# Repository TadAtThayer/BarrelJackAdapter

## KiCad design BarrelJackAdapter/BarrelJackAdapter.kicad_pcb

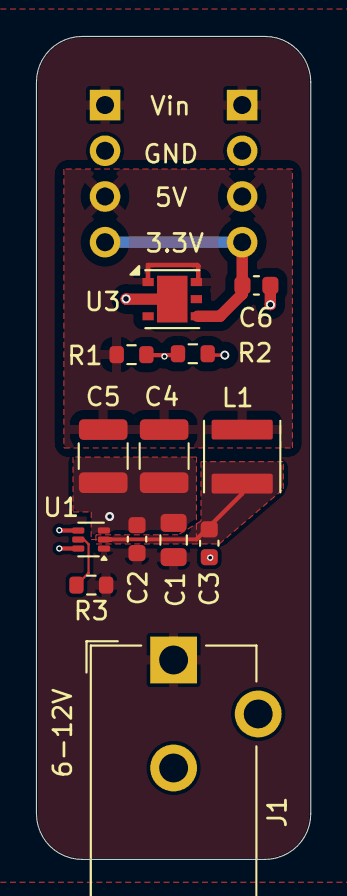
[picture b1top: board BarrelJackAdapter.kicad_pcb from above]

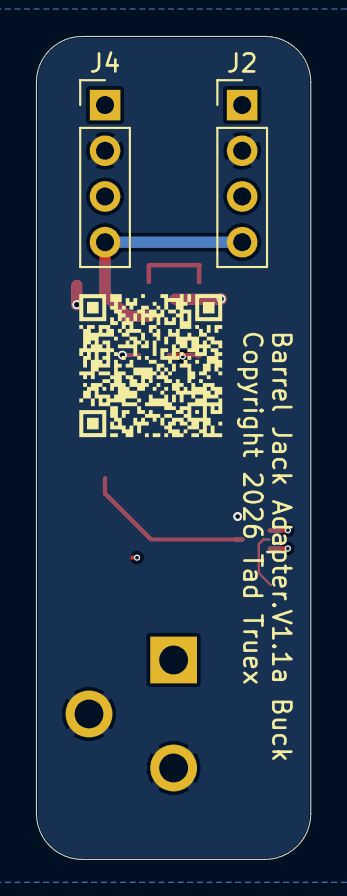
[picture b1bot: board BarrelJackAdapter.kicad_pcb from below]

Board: 4 copper layers, 15.2 x 45.7 mm, 15 parts (2 on the bottom side), 8 nets.

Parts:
C1: 10u; C_0805_2012Metric
C2, C3: .1u; C_0603_1608Metric
C4, C5: 22u; C_1210_3225Metric
C6: 4.7u; C_0603_1608Metric
J1: Barrel_Jack_Switch; BarrelJack_CUI_PJ-102AH_Horizontal
J2, J4: Conn_01x04; PinHeader_1x04_P2.54mm_Vertical
L1: 10uH; L_Abracon_ASPI-4030S
R1: 49.9k; R_0603_1608Metric
R2, R3: 10k; R_0603_1608Metric
U1: TPS563206DRLR; SOT-563
U3: LDL112PV33R; DFN-6-1EP_3x3mm_P0.95mm_EP1.7x2.6mm

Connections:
+3.3V: C6.1, J2.4, J4.4, U3.4 (VOUT)
+5V: C4.1, C5.1, J2.3, J4.3, L1.2, R1.1, U3.1 (EN), U3.6 (VIN)
+9V: C1.1, C2.1, J1.1, J2.1, J4.1, R3.1, U1.1 (VIN)
/BST: C3.1, U1.4 (BST)
/FB: R1.2, R2.2, U1.6 (FB)
/SW: C3.2, L1.1, U1.2 (SW)
GND: C1.2, C2.2, C4.2, C5.2, C6.2, J1.2, J1.3, J2.2, J4.2, R2.1, U1.3 (GND), U3.2 (GND), U3.7 (EPAD)
unnamed: R3.2, U1.5 (EN)

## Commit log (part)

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2024-11-07 add small breakout for reg.
2024-11-15 Small board to hold a barrel jack on a breadboard. Through holes for a T0-223 regulator (eg an L7805)
2024-11-15 Less agressive rev number - this is 0.1
2024-11-15 new rev of barrel jack. Now with more complication!
2024-11-15 wip v2
2024-11-15 V1.0 artwork
2024-11-15 V1.0 now more silk!
2024-12-13 working on an SMD version of the little adapter
2024-12-13 ignore more stuff
2024-12-13 add some silkscreen
2024-12-14 first rev of buck converter based version.
2024-12-14 add 3.3v LDO
2024-12-16 Remove some vias to the back ground plane.
    Localize the high current loop to Front Copper.
    Move the switch node connection to Cu2 - sandwich
    between clean ground pours.
2024-12-20 Initial version of Buck Converter
2025-01-08 Fix schematic.
    Better Layout
    Close #2
2025-12-15 Work on BOM.
    Be very skeptical of this checkin. There were some merge shenanigans involved.

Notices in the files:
BarrelJackAdapter/BarrelJackAdapter.kicad_pcb:
Copyright 2026 Tad Truex
